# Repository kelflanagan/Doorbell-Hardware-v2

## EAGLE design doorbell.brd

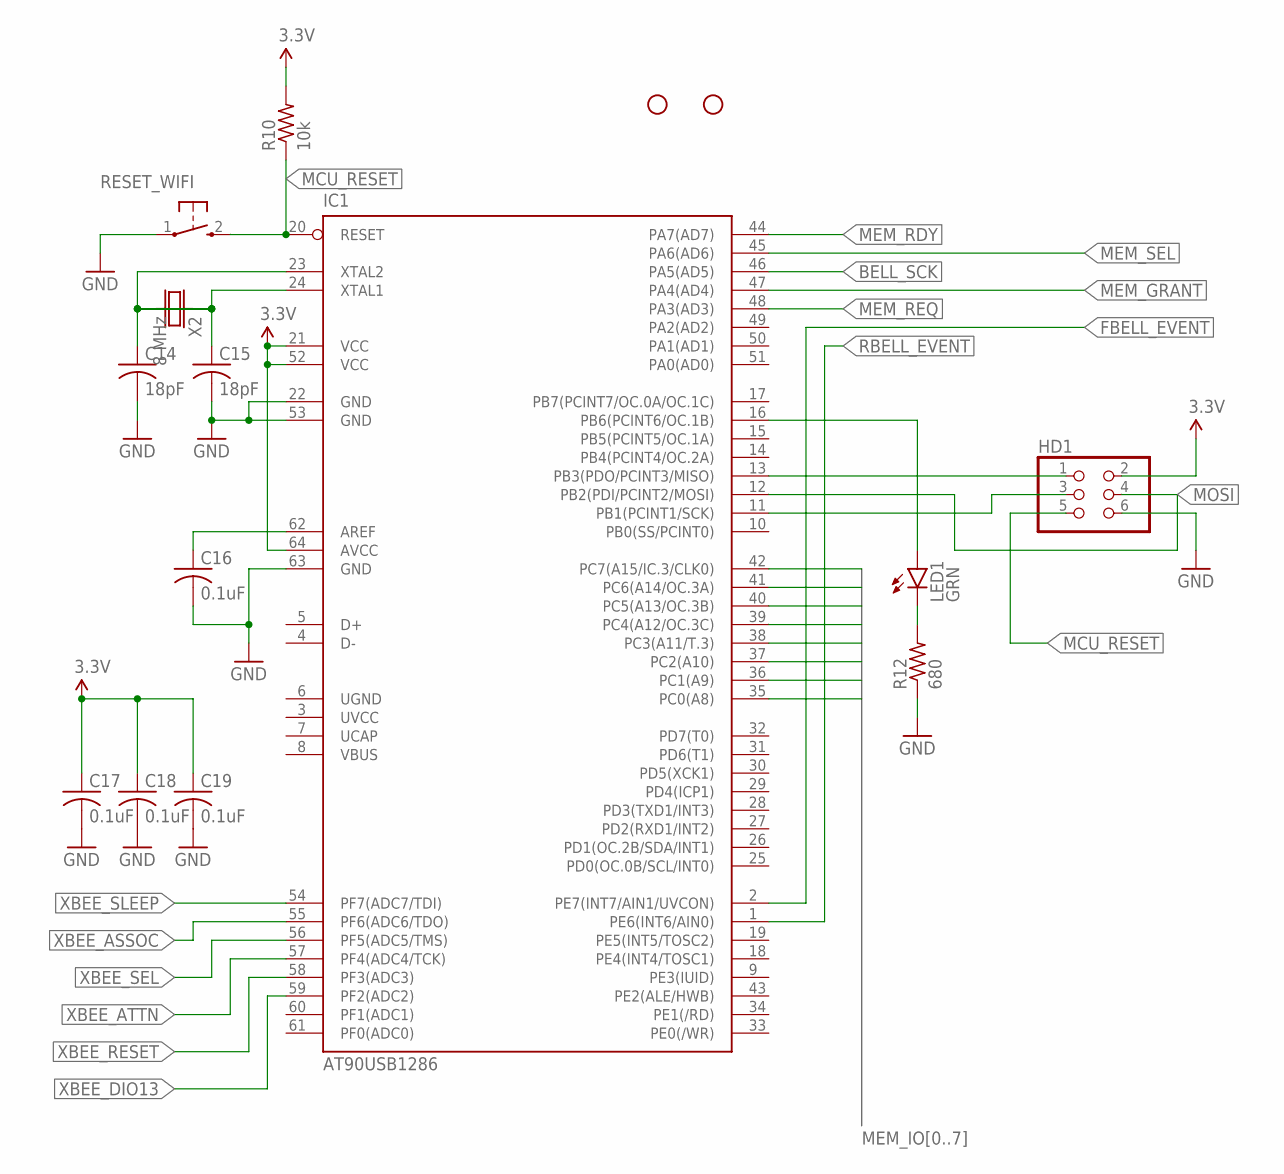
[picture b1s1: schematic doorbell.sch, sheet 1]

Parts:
C14, C15: 18pF; 0603_CAP
C16, C17, C18, C19: 0.1uF; 0603_CAP
HD1: HEADER_2X3
IC1: AT90USB1286; TQFP64
JP1, JP3: STAND-OFF
LED1: GRN; 0603_LED
R10: 10k; 0603_RESISTOR
R12: 680; 0603_RESISTOR
RESET_WIFI: SWITCH; SWITCH_TAC
X2: 8 MHz; CRYSTAL_5X3

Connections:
3.3V: C17.1, C18.1, C19.1, HD1.2, IC1.21 (VCC), IC1.52 (VCC), IC1.64 (AVCC), R10.2; also elsewhere on the board
BELL_SCK: IC1.46 (PA5(AD5)); also elsewhere on the board
FBELL_EVENT: IC1.2 (PE7(INT7/AIN1/UVCON)); also elsewhere on the board
GND: C14.2, C15.2, C16.2, C17.2, C18.2, C19.2, HD1.6, IC1.22 (GND), IC1.53 (GND), IC1.63 (GND), R12.1, RESET_WIFI.1; also elsewhere on the board
MCU_RESET: HD1.5, IC1.20 (RESET), R10.1, RESET_WIFI.2
MEM_GRANT: IC1.47 (PA4(AD4)); also elsewhere on the board
MEM_IO0: IC1.35 (PC0(A8)); also elsewhere on the board
MEM_IO1: IC1.36 (PC1(A9)); also elsewhere on the board
MEM_IO2: IC1.37 (PC2(A10)); also elsewhere on the board
MEM_IO3: IC1.38 (PC3(A11/T.3)); also elsewhere on the board
MEM_IO4: IC1.39 (PC4(A12/OC.3C)); also elsewhere on the board
MEM_IO5: IC1.40 (PC5(A13/OC.3B)); also elsewhere on the board
MEM_IO6: IC1.41 (PC6(A14/OC.3A)); also elsewhere on the board
MEM_IO7: IC1.42 (PC7(A15/IC.3/CLK0)); also elsewhere on the board
MEM_RDY: IC1.44 (PA7(AD7)); also elsewhere on the board
MEM_REQ: IC1.48 (PA3(AD3)); also elsewhere on the board
MEM_SEL: IC1.45 (PA6(AD6)); also elsewhere on the board
MISO: HD1.1, IC1.13 (PB3(PDO/PCINT3/MISO)); also elsewhere on the board
MOSI: HD1.4, IC1.12 (PB2(PDI/PCINT2/MOSI)); also elsewhere on the board
unnamed: C14.1, IC1.23 (XTAL2), X2.1
unnamed: C15.1, IC1.24 (XTAL1), X2.2
unnamed: LED1.C, R12.2
unnamed: IC1.16 (PB6(PCINT6/OC.1B)), LED1.A
unnamed: C16.1, IC1.62 (AREF)
RBELL_EVENT: IC1.1 (PE6(INT6/AIN0)); also elsewhere on the board
SCK: HD1.3, IC1.11 (PB1(PCINT1/SCK)); also elsewhere on the board
UCAP: IC1.7 (UCAP)
UGND: IC1.6 (UGND)
UVCC: IC1.3 (UVCC)
VBUS: IC1.8 (VBUS)
XBEE_ASSOC: IC1.55 (PF6(ADC6/TDO)); also elsewhere on the board
XBEE_ATTN: IC1.57 (PF4(ADC4/TCK)); also elsewhere on the board
XBEE_DIO13: IC1.59 (PF2(ADC2)); also elsewhere on the board
XBEE_RESET: IC1.58 (PF3(ADC3)); also elsewhere on the board
XBEE_SEL: IC1.56 (PF5(ADC5/TMS)); also elsewhere on the board
XBEE_SLEEP: IC1.54 (PF7(ADC7/TDI)); also elsewhere on the board

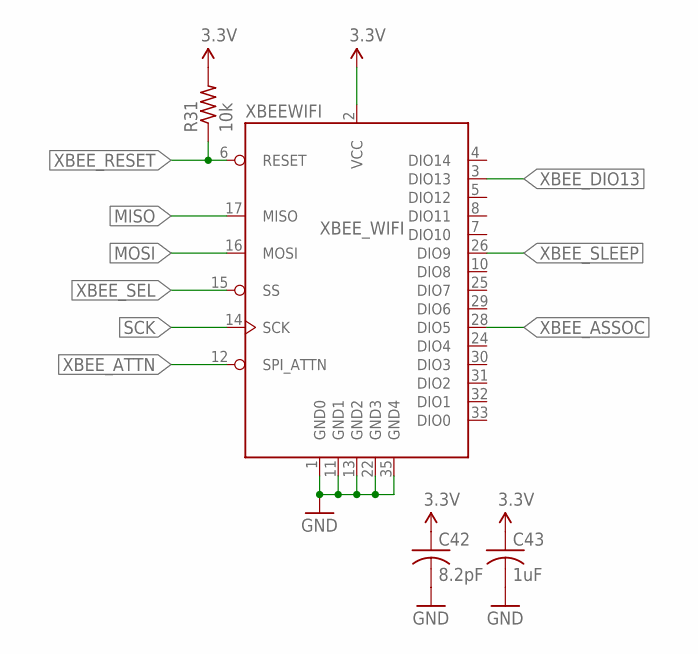
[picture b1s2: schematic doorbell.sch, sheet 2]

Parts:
C42: 8.2pF; 0603_CAP
C43: 1uF; 0603_CAP
R31: 10k; 0603_RESISTOR
XBEEWIFI: XBEE_WIFI

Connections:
3.3V: C42.1, C43.1, R31.2, XBEEWIFI.2 (VCC); also elsewhere on the board
GND: C42.2, C43.2, XBEEWIFI.1 (GND0), XBEEWIFI.11 (GND1), XBEEWIFI.13 (GND2), XBEEWIFI.22 (GND3), XBEEWIFI.35 (GND4); also elsewhere on the board
MISO: XBEEWIFI.17 (MISO); also elsewhere on the board
MOSI: XBEEWIFI.16 (MOSI); also elsewhere on the board
SCK: XBEEWIFI.14 (SCK); also elsewhere on the board
XBEE_ASSOC: XBEEWIFI.28 (DIO5); also elsewhere on the board
XBEE_ATTN: XBEEWIFI.12 (SPI_ATTN); also elsewhere on the board
XBEE_DIO13: XBEEWIFI.3 (DIO13); also elsewhere on the board
XBEE_RESET: R31.1, XBEEWIFI.6 (RESET); also elsewhere on the board
XBEE_SEL: XBEEWIFI.15 (SS); also elsewhere on the board
XBEE_SLEEP: XBEEWIFI.26 (DIO9); also elsewhere on the board

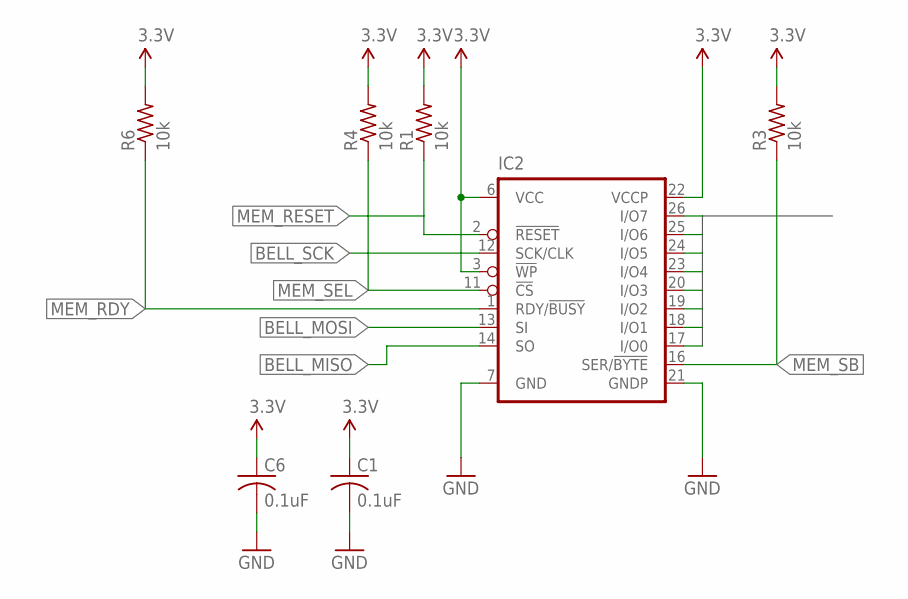
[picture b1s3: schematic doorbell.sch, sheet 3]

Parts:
C1, C6: 0.1uF; 0603_CAP
IC2: AT45DB642D; 28T-TSOP-1
R1, R3, R4, R6: 10k; 0603_RESISTOR

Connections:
3.3V: C1.1, C6.1, IC2.3 (!WP), IC2.6 (VCC), IC2.22 (VCCP), R1.2, R3.2, R4.2, R6.2; also elsewhere on the board
BELL_MISO: IC2.14 (SO); also elsewhere on the board
BELL_MOSI: IC2.13 (SI); also elsewhere on the board
BELL_SCK: IC2.12 (SCK/CLK); also elsewhere on the board
GND: C1.2, C6.2, IC2.7 (GND), IC2.21 (GNDP); also elsewhere on the board
MEM_IO0: IC2.17 (I/O0); also elsewhere on the board
MEM_IO1: IC2.18 (I/O1); also elsewhere on the board
MEM_IO2: IC2.19 (I/O2); also elsewhere on the board
MEM_IO3: IC2.20 (I/O3); also elsewhere on the board
MEM_IO4: IC2.23 (I/O4); also elsewhere on the board
MEM_IO5: IC2.24 (I/O5); also elsewhere on the board
MEM_IO6: IC2.25 (I/O6); also elsewhere on the board
MEM_IO7: IC2.26 (I/O7); also elsewhere on the board
MEM_RDY: IC2.1 (RDY/!BUSY), R6.1; also elsewhere on the board
MEM_RESET: IC2.2 (!RESET), R1.1; also elsewhere on the board
MEM_SB: IC2.16 (SER/!BYTE), R3.1; also elsewhere on the board
MEM_SEL: IC2.11 (!CS), R4.1; also elsewhere on the board

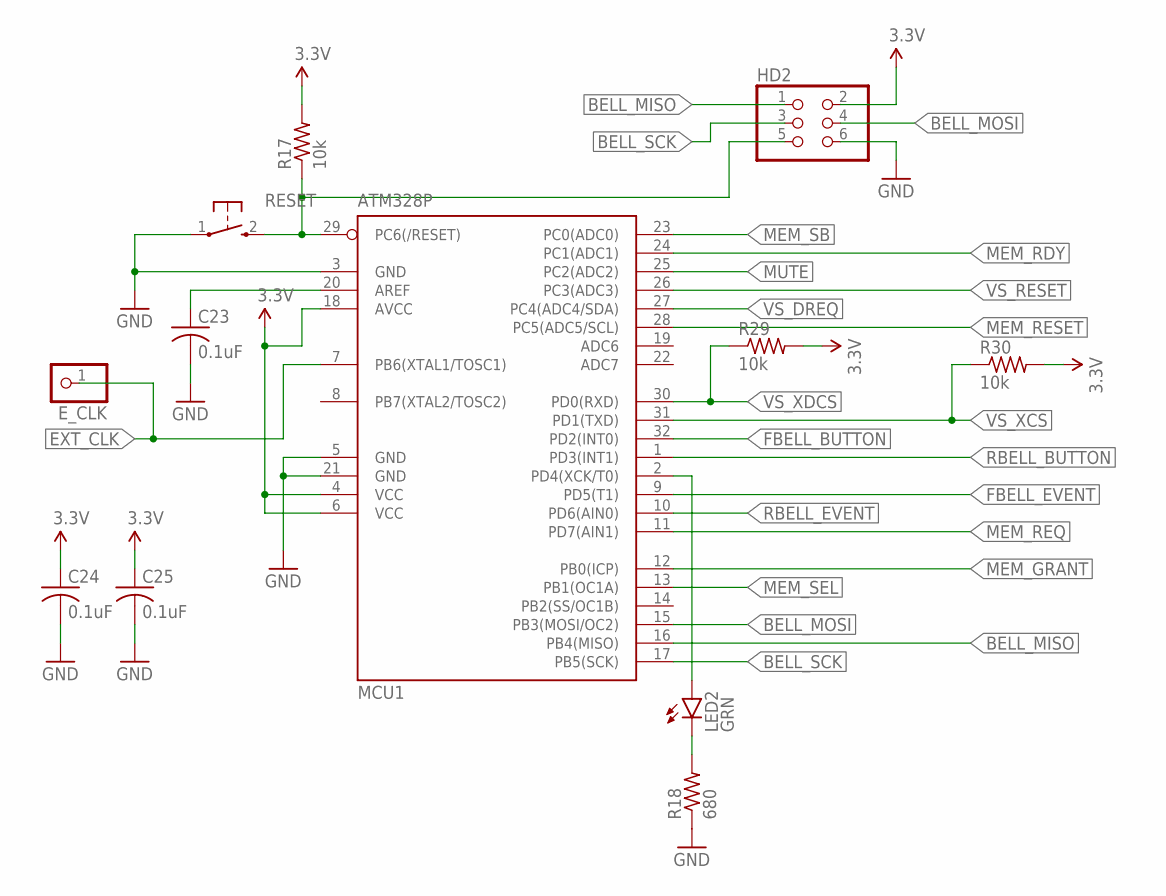
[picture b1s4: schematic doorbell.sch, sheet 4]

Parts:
C23, C24, C25: 0.1uF; 0603_CAP
E_CLK: PINHD-1X1; 1X01
HD2: HEADER_2X3
LED2: GRN; 0603_LED
MCU1: ATM328P; TQFP32-08
R17, R29, R30: 10k; 0603_RESISTOR
R18: 680; 0603_RESISTOR
RESET: SWITCH; SWITCH_TAC

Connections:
3.3V: C24.1, C25.1, HD2.2, MCU1.4 (VCC), MCU1.6 (VCC), MCU1.18 (AVCC), R17.2, R29.2, R30.2; also elsewhere on the board
BELL_MISO: HD2.1, MCU1.16 (PB4(MISO)); also elsewhere on the board
BELL_MOSI: HD2.4, MCU1.15 (PB3(MOSI/OC2)); also elsewhere on the board
BELL_RESET: HD2.5, MCU1.29 (PC6(/RESET)), R17.1, RESET.2
BELL_SCK: HD2.3, MCU1.17 (PB5(SCK)); also elsewhere on the board
EXT_CLK: E_CLK.1, MCU1.7 (PB6(XTAL1/TOSC1))
FBELL_BUTTON: MCU1.32 (PD2(INT0)); also elsewhere on the board
FBELL_EVENT: MCU1.9 (PD5(T1)); also elsewhere on the board
GND: C23.2, C24.2, C25.2, HD2.6, MCU1.3 (GND), MCU1.5 (GND), MCU1.21 (GND), R18.1, RESET.1; also elsewhere on the board
MEM_GRANT: MCU1.12 (PB0(ICP)); also elsewhere on the board
MEM_RDY: MCU1.24 (PC1(ADC1)); also elsewhere on the board
MEM_REQ: MCU1.11 (PD7(AIN1)); also elsewhere on the board
MEM_RESET: MCU1.28 (PC5(ADC5/SCL)); also elsewhere on the board
MEM_SB: MCU1.23 (PC0(ADC0)); also elsewhere on the board
MEM_SEL: MCU1.13 (PB1(OC1A)); also elsewhere on the board
MUTE: MCU1.25 (PC2(ADC2)); also elsewhere on the board
unnamed: C23.1, MCU1.20 (AREF)
unnamed: LED2.C, R18.2
unnamed: LED2.A, MCU1.2 (PD4(XCK/T0))
RBELL_BUTTON: MCU1.1 (PD3(INT1)); also elsewhere on the board
RBELL_EVENT: MCU1.10 (PD6(AIN0)); also elsewhere on the board
VS_DREQ: MCU1.27 (PC4(ADC4/SDA)); also elsewhere on the board
VS_RESET: MCU1.26 (PC3(ADC3)); also elsewhere on the board
VS_XCS: MCU1.31 (PD1(TXD)), R30.1; also elsewhere on the board
VS_XDCS: MCU1.30 (PD0(RXD)), R29.1; also elsewhere on the board

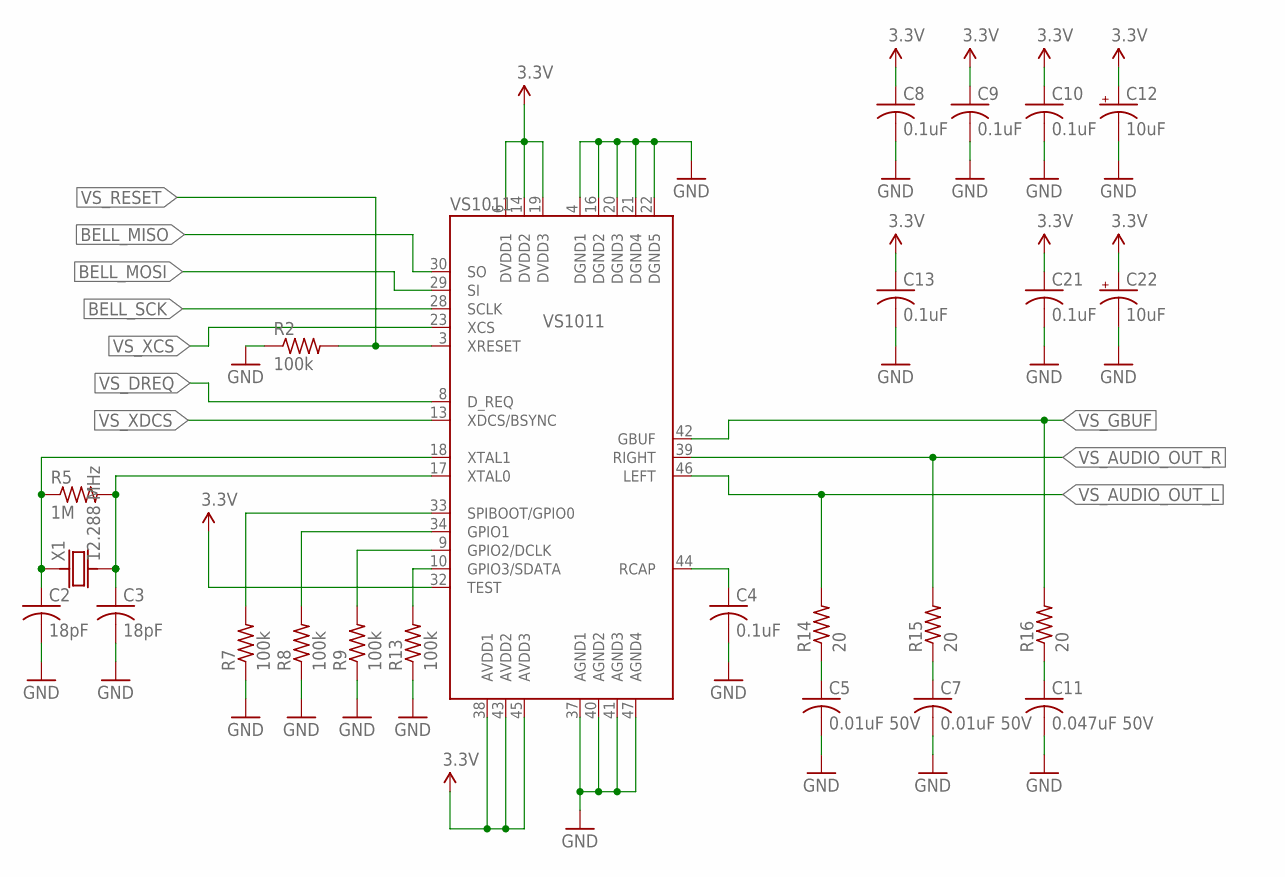
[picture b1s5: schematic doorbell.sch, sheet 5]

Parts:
C2, C3: 18pF; 0603_CAP
C4, C8, C9, C10, C13, C21: 0.1uF; 0603_CAP
C5, C7: 0.01uF 50V; 0603_CAP
C11: 0.047uF 50V; 0603_CAP
C12, C22: 10uF; B_CAP
R2, R7, R8, R9, R13: 100k; 0603_RESISTOR
R5: 1M; 0603_RESISTOR
R14, R15, R16: 20; 0603_RESISTOR
VS1011: VS1011; LQFP-48
X1: 12.288 MHz; CRYSTAL_5X3

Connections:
3.3V: C8.1, C9.1, C10.1, C12.+, C13.1, C21.1, C22.+, VS1011.6 (DVDD1), VS1011.14 (DVDD2), VS1011.19 (DVDD3), VS1011.32 (TEST), VS1011.38 (AVDD1), VS1011.43 (AVDD2), VS1011.45 (AVDD3); also elsewhere on the board
BELL_MISO: VS1011.30 (SO); also elsewhere on the board
BELL_MOSI: VS1011.29 (SI); also elsewhere on the board
BELL_SCK: VS1011.28 (SCLK); also elsewhere on the board
GND: C2.2, C3.2, C4.2, C5.2, C7.2, C8.2, C9.2, C10.2, C11.2, C12.-, C13.2, C21.2, C22.-, R2.1, R7.1, R8.1, R9.1, R13.1, VS1011.4 (DGND1), VS1011.16 (DGND2), VS1011.20 (DGND3), VS1011.21 (DGND4), VS1011.22 (DGND5), VS1011.37 (AGND1), VS1011.40 (AGND2), VS1011.41 (AGND3), VS1011.47 (AGND4); also elsewhere on the board
unnamed: C2.1, R5.1, VS1011.18 (XTAL1), X1.1
unnamed: C3.1, R5.2, VS1011.17 (XTAL0), X1.2
unnamed: C4.1, VS1011.44 (RCAP)
unnamed: R13.2, VS1011.10 (GPIO3/SDATA)
unnamed: R9.2, VS1011.9 (GPIO2/DCLK)
unnamed: R8.2, VS1011.34 (GPIO1)
unnamed: R7.2, VS1011.33 (SPIBOOT/GPIO0)
unnamed: C5.1, R14.1
unnamed: C7.1, R15.1
unnamed: C11.1, R16.1
VS_AUDIO_OUT_L: R14.2, VS1011.46 (LEFT); also elsewhere on the board
VS_AUDIO_OUT_R: R15.2, VS1011.39 (RIGHT)
VS_DREQ: VS1011.8 (D_REQ); also elsewhere on the board
VS_GBUF: R16.2, VS1011.42 (GBUF)
VS_RESET: R2.2, VS1011.3 (XRESET); also elsewhere on the board
VS_XCS: VS1011.23 (XCS); also elsewhere on the board
VS_XDCS: VS1011.13 (XDCS/BSYNC); also elsewhere on the board

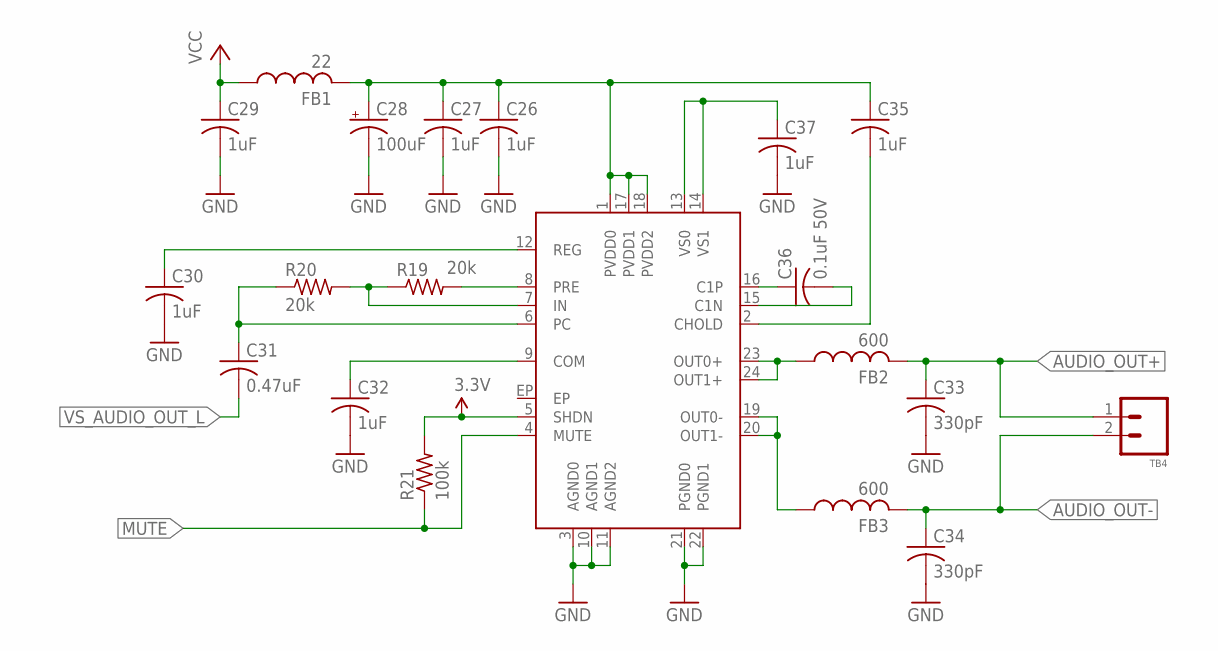
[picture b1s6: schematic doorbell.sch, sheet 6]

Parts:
C26, C27, C29, C35: 1uF; 0805_CAP
C28: 100uF; F_CAP
C30, C32, C37: 1uF; 0603_CAP
C31: 0.47uF; 0603_CAP
C33, C34: 330pF; 0603_CAP
C36: 0.1uF 50V; 0603_CAP
FB1: 22; 0805_FB
FB2, FB3: 600; 0805_FB
MAX1: MAX9737; TQFN24
R19, R20: 20k; 0603_RESISTOR
R21: 100k; 0603_RESISTOR
TB4: TERMINAL_BLOCK_2

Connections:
3.3V: MAX1.5 (SHDN), R21.2; also elsewhere on the board
AUDIO_OUT+: C33.1, FB2.2, TB4.1
AUDIO_OUT-: C34.1, FB3.2, TB4.2
GND: C26.2, C27.2, C28.-, C29.2, C30.2, C32.2, C33.2, C34.2, C37.2, MAX1.3 (AGND0), MAX1.10 (AGND1), MAX1.11 (AGND2), MAX1.21 (PGND0), MAX1.22 (PGND1); also elsewhere on the board
MUTE: MAX1.4 (MUTE), R21.1; also elsewhere on the board
unnamed: C26.1, C27.1, C28.+, C35.1, FB1.2, MAX1.1 (PVDD0), MAX1.17 (PVDD1), MAX1.18 (PVDD2)
unnamed: C30.1, MAX1.12 (REG)
unnamed: MAX1.8 (PRE), R19.2
unnamed: MAX1.7 (IN), R19.1, R20.2
unnamed: C31.1, MAX1.6 (PC), R20.1
unnamed: C32.1, MAX1.9 (COM)
unnamed: FB3.1, MAX1.19 (OUT0-), MAX1.20 (OUT1-)
unnamed: FB2.1, MAX1.23 (OUT0+), MAX1.24 (OUT1+)
unnamed: C35.2, MAX1.2 (CHOLD)
unnamed: C36.1, MAX1.16 (C1P)
unnamed: C36.2, MAX1.15 (C1N)
unnamed: C37.1, MAX1.13 (VS0), MAX1.14 (VS1)
VCC: C29.1, FB1.1; also elsewhere on the board
VS_AUDIO_OUT_L: C31.2; also elsewhere on the board

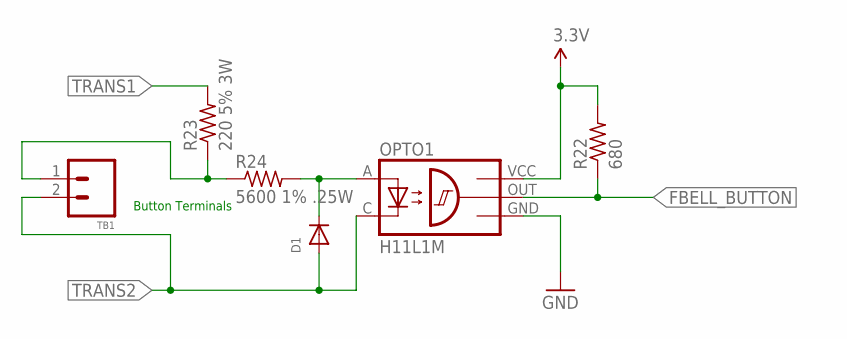
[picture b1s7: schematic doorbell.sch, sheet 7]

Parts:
D1: DIODE0603; 0603_DIODE
OPTO1: H11L1M; SOIC6
R22: 680; 0603_RESISTOR
R23: 220 5% 3W; 4122_RESISTOR
R24: 5600 1% .25W; 1206_RESISTOR
TB1: TERMINAL_BLOCK_2

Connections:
3.3V: OPTO1.VCC, R22.2; also elsewhere on the board
FBELL_BUTTON: OPTO1.OUT, R22.1; also elsewhere on the board
GND: OPTO1.GND; also elsewhere on the board
unnamed: D1.C, OPTO1.A, R24.2
unnamed: R23.1, R24.1, TB1.1
TRANS1: R23.2; also elsewhere on the board
TRANS2: D1.A, OPTO1.C, TB1.2; also elsewhere on the board

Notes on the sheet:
Button Terminals

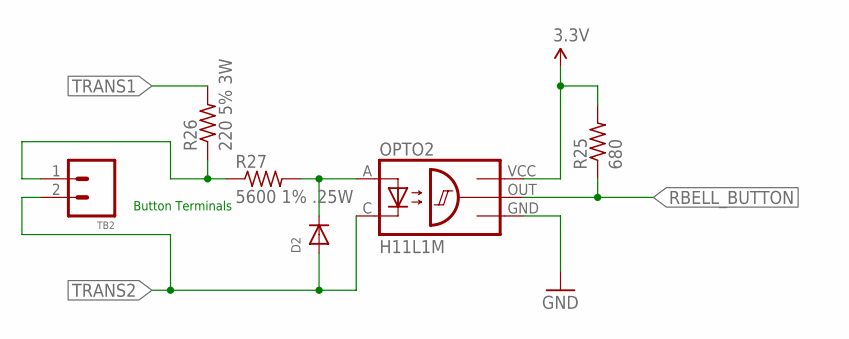
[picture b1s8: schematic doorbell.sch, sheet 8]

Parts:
D2: DIODE0603; 0603_DIODE
OPTO2: H11L1M; SOIC6
R25: 680; 0603_RESISTOR
R26: 220 5% 3W; 4122_RESISTOR
R27: 5600 1% .25W; 1206_RESISTOR
TB2: TERMINAL_BLOCK_2

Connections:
3.3V: OPTO2.VCC, R25.2; also elsewhere on the board
GND: OPTO2.GND; also elsewhere on the board
unnamed: D2.C, OPTO2.A, R27.2
unnamed: R26.1, R27.1, TB2.1
RBELL_BUTTON: OPTO2.OUT, R25.1; also elsewhere on the board
TRANS1: R26.2; also elsewhere on the board
TRANS2: D2.A, OPTO2.C, TB2.2; also elsewhere on the board

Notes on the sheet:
Button Terminals

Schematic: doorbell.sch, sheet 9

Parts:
B1: BR; DFS
C38, C41: 1500uF; J16_CAP
C39: 100uF; F_CAP
C40: 330uF; F_CAP
L1: 1mH; DR125
LED3: GRN; 0603_LED
R28: 680; 0603_RESISTOR
REG1: TL2575; TO-263-5
TB3: TERMINAL_BLOCK_2
Z1: SCHOTTKY_DIODE; SMD_DIODE

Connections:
3.3V: C40.+, L1.2, R28.2, REG1.4 (FB); also elsewhere on the board
GND: B1.-, C38.-, C39.-, C40.-, C41.-, LED3.C, REG1.3 (GND), REG1.5 (ON/OFF), Z1.A; also elsewhere on the board
unnamed: L1.1, REG1.2 (OUT), Z1.C
unnamed: LED3.A, R28.1
TRANS1: B1.AC2, TB3.1; also elsewhere on the board
TRANS2: B1.AC1, TB3.2; also elsewhere on the board
VCC: B1.+, C38.+, C39.+, C41.+, REG1.1 (VIN); also elsewhere on the board

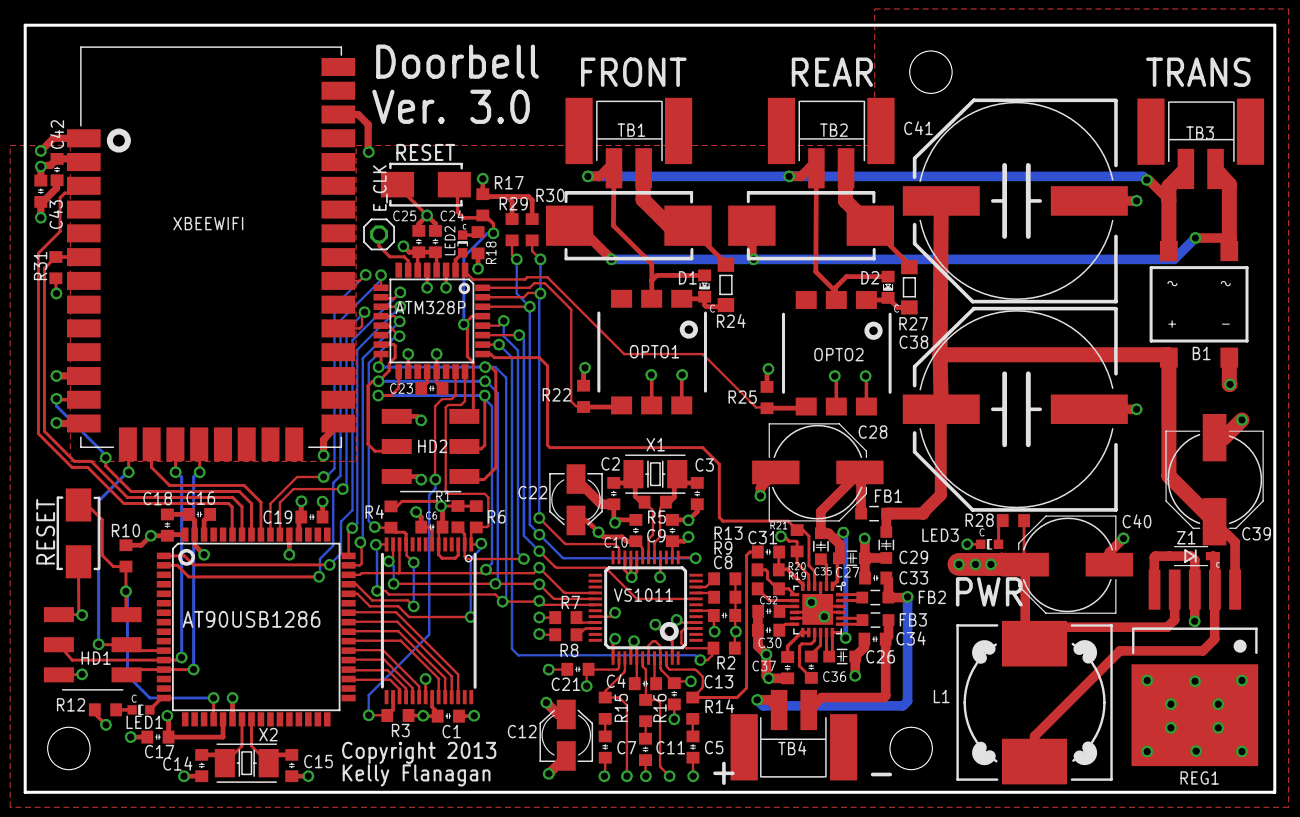
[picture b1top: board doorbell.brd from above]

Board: 4 copper layers, 105.5 x 64.8 mm, 106 parts (0 on the bottom side), 84 nets.

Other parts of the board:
JP2: STAND-OFF

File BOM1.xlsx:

Part | Value | Device | Package
R14 | 20 | RESISTOR0603 | 0603_RESISTOR
R15 | 20 | RESISTOR0603 | 0603_RESISTOR
R16 | 20 | RESISTOR0603 | 0603_RESISTOR
FB1 | 22 | FB0805 | 0805_FB
FB2 | 600 | FB0805 | 0805_FB
FB3 | 600 | FB0805 | 0805_FB
R12 | 680 | RESISTOR0603 | 0603_RESISTOR
R18 | 680 | RESISTOR0603 | 0603_RESISTOR
R22 | 680 | RESISTOR0603 | 0603_RESISTOR
R25 | 680 | RESISTOR0603 | 0603_RESISTOR
R28 | 680 | RESISTOR0603 | 0603_RESISTOR
C5 | 0.01uF 50V | CAP0603 | 0603_CAP
C7 | 0.01uF 50V | CAP0603 | 0603_CAP
C11 | 0.047uF 50V | CAP0603 | 0603_CAP
C1 | 0.1uF | CAP0603 | 0603_CAP
C4 | 0.1uF | CAP0603 | 0603_CAP
C6 | 0.1uF | CAP0603 | 0603_CAP
C8 | 0.1uF | CAP0603 | 0603_CAP
C9 | 0.1uF | CAP0603 | 0603_CAP
C10 | 0.1uF | CAP0603 | 0603_CAP
C13 | 0.1uF | CAP0603 | 0603_CAP
C16 | 0.1uF | CAP0603 | 0603_CAP
C17 | 0.1uF | CAP0603 | 0603_CAP
C18 | 0.1uF | CAP0603 | 0603_CAP
C19 | 0.1uF | CAP0603 | 0603_CAP
C21 | 0.1uF | CAP0603 | 0603_CAP
C23 | 0.1uF | CAP0603 | 0603_CAP
C24 | 0.1uF | CAP0603 | 0603_CAP
C25 | 0.1uF | CAP0603 | 0603_CAP
C36 | 0.1uF 50V | CAP0603 | 0603_CAP
C31 | 0.47uF | CAP0603 | 0603_CAP
R2 | 100k | RESISTOR0603 | 0603_RESISTOR
R7 | 100k | RESISTOR0603 | 0603_RESISTOR
R8 | 100k | RESISTOR0603 | 0603_RESISTOR
R9 | 100k | RESISTOR0603 | 0603_RESISTOR
R13 | 100k | RESISTOR0603 | 0603_RESISTOR
R21 | 100k | RESISTOR0603 | 0603_RESISTOR
C28 | 100uF | CAP_POLF | F_CAP
C39 | 100uF | CAP_POLF | F_CAP
R1 | 10k | RESISTOR0603 | 0603_RESISTOR
R3 | 10k | RESISTOR0603 | 0603_RESISTOR
R4 | 10k | RESISTOR0603 | 0603_RESISTOR
R6 | 10k | RESISTOR0603 | 0603_RESISTOR
R10 | 10k | RESISTOR0603 | 0603_RESISTOR
R17 | 10k | RESISTOR0603 | 0603_RESISTOR
R29 | 10k | RESISTOR0603 | 0603_RESISTOR
R30 | 10k | RESISTOR0603 | 0603_RESISTOR
R31 | 10k | RESISTOR0603 | 0603_RESISTOR
C12 | 10uF | CAP_POLB | B_CAP
C22 | 10uF | CAP_POLB | B_CAP
X1 | 12.288 MHz | CRYSTAL5X3 | CRYSTAL_5X3
C38 | 1500uF | CAP_POLJ16 | J16_CAP
C41 | 1500uF | CAP_POLJ16 | J16_CAP
C2 | 18pF | CAP0603 | 0603_CAP
C3 | 18pF | CAP0603 | 0603_CAP
C14 | 18pF | CAP0603 | 0603_CAP
C15 | 18pF | CAP0603 | 0603_CAP
R5 | 1M | RESISTOR0603 | 0603_RESISTOR
L1 | 1mH | DR125 | DR125
C30 | 1uF | CAP0603 | 0603_CAP
C32 | 1uF | CAP0603 | 0603_CAP
C37 | 1uF | CAP0603 | 0603_CAP
C43 | 1uF | CAP0603 | 0603_CAP
C26 | 1uF | CAP0805 | 0805_CAP
C27 | 1uF | CAP0805 | 0805_CAP
C29 | 1uF | CAP0805 | 0805_CAP
C35 | 1uF | CAP0805 | 0805_CAP
R19 | 20k | RESISTOR0603 | 0603_RESISTOR
R20 | 20k | RESISTOR0603 | 0603_RESISTOR
R23 | 220 5% 3W | RESISTOR4122 | 4122_RESISTOR
R26 | 220 5% 3W | RESISTOR4122 | 4122_RESISTOR
C33 | 330pF | CAP0603 | 0603_CAP
C34 | 330pF | CAP0603 | 0603_CAP
C40 | 330uF | CAP_POLF | F_CAP
R24 | 5600 1% .25W | RESISTOR1206 | 1206_RESISTOR
R27 | 5600 1% .25W | RESISTOR1206 | 1206_RESISTOR
X2 | 8 MHz | CRYSTAL5X3 | CRYSTAL_5X3
C42 | 8.2pF | CAP0603 | 0603_CAP
IC1 | AT90USB1286 | AT90USB1286 | TQFP64
MCU1 | ATM328P | ATMEGA328P | TQFP32-08
LED1 | GRN | LED0603 | 0603_LED
LED2 | GRN | LED0603 | 0603_LED
LED3 | GRN | LED0603 | 0603_LED
OPTO1 | H11L1M | H11L1M | SOIC6
OPTO2 | H11L1M | H11L1M | SOIC6
HD1 | HEADER_2X3 | HEADER_2X3 | HEADER_2X3
HD2 | HEADER_2X3 | HEADER_2X3 | HEADER_2X3
MAX1 | MAX9737 | MAX9737 | TQFN24
TB1 | TERMINAL_BLOCK_2 | TERMINAL_BLOCK_2 | TERMINAL_BLOCK_2
TB2 | TERMINAL_BLOCK_2 | TERMINAL_BLOCK_2 | TERMINAL_BLOCK_2
TB3 | TERMINAL_BLOCK_2 | TERMINAL_BLOCK_2 | TERMINAL_BLOCK_2
TB4 | TERMINAL_BLOCK_2 | TERMINAL_BLOCK_2 | TERMINAL_BLOCK_2
VS1011 | VS1011 | VS1011 | LQFP-48
XBEEWIFI | XBEE_WIFI | XBEE_WIFI | XBEE_WIFI
IC2 |  | AT45DB642D | 28T-TSOP-1
B1 |  | BR | DFS
D1 |  | DIODE0603 | 0603_DIODE
D2 |  | DIODE0603 | 0603_DIODE
Z1 |  | SCHOTTKY_DIODE | SMD_DIODE
RESET |  | SWITCH | SWITCH_TAC
RESET_WIFI |  | SWITCH | SWITCH_TAC
REG1 |  | TL2575 | TO-263-5

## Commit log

2016-05-04 Frist commit

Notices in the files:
doorbell.brd:
Copyright 2013
parts and their libraries:
SparkFun-Electromechanical: Licensing: CC v3.0 Share-Alike You are welcome to use this library for commercial purposes.
